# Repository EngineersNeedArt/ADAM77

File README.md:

# Adam77

A 40×24 ASCII serial terminal for early 8-bit computers such as the KIM-1. A USB keyboard plugs into the Teensy 4.1's USB host port. Text appears on a 320×240 ILI9341 TFT.

Adam77 follows [Adam74](https://github.com/EngineersNeedArt/Adam74). Adam74 took parallel ASCII in; Adam77 talks serial and adds a keyboard.

## Layout

| Path | What |
| --- | --- |
| `src/main.cpp` | Firmware |
| `lib/TextBuffer/` | Text grid class, from Adam74 |
| `lib/Fonts/` | Liberation Mono Bold, from Adam74 |
| `hardware/` | KiCad project (rough schematic; see below) |
| `platformio.ini` | Build configuration |

## Building

```bash
pio run              # build
pio run -t upload    # build and flash (Teensy Loader opens)
pio device monitor   # USB debug console
```

## Hardware (KiCad)

`hardware/ADAM77.kicad_pro` opens in KiCad 10. It's a rough first pass, generated rather than drawn by hand, so expect to tidy the layout.

- **The schematic** covers USB-C 5 V input (with CC pull-downs), the Teensy 4.1, the PAL-2 TTL header (74HC4050 on the PAL-2's output, polyfuse on its 5 V), the TFT header, the USB host jack and the LM386 audio section.
- **ERC:** no errors or warnings.
- **Through-hole parts** everywhere except the USB-C jack, whose six power-only pads are large enough to hand-solder. The level shifter is a **74HC4050** (DIP-16) instead of the 74LVC245, which isn't made in DIP. Powered at 3.3 V, its inputs accept 5 V and its outputs are 3.3 V. The polyfuse is the radial Bourns MF-RG1100.
- **The Teensy 4.1** symbol and footprint are in the project's own library (`ADAM77.kicad_sym`, `ADAM77.pretty`). The footprint covers the 48 outer pins only. The USB host pins come out on J4, a 5-pin header for a short cable from the Teensy, since their exact position on the Teensy isn't modeled.
- **To start the PCB:** open the PCB editor and choose Tools → Update PCB from Schematic (F8) to pull in all the footprints.
- **J2 (PAL-2):** 1 GND, 2 +5V, 3 `TTL (IN) KYBD`, 4 `TTL (OUT) PTR`. The PAL-2 has no standard cable, so make a 4-wire one to match.
- **J4 (USB host):** 5V, D−, D+, GND, GND, the same order as the Teensy 4.1's host pins.

## Loading files from the SD card

Put files on a microSD card (FAT16, FAT32 or exFAT), in folders if you like, and put it in the Teensy 4.1's own card socket. [sd/](sd/) has a ready-made set of KIM-1 paper tapes to copy onto a card. Cards can be swapped while Adam77 is on, as long as nothing is being sent.

1. At the KIM-1 monitor prompt, press **F2**. A list of the card's folders and files appears, folders first (in white, labeled FOLDER). The top line shows the folder you're in. Known types show their name without the extension, plus a type label. Files that are sent (TAPE, BASIC) are green; text files, which are only read, are dark green. The banners and the startup message are white. The selection bar is the selected entry's own color, inverted.
2. Choose one with the arrow keys (Page Up/Down and Home/End also work; holding an arrow repeats it), or type a letter or digit to jump to the next name starting with it. Then press **Enter**.
   - **Enter** (or Right arrow) on a folder opens it. **Esc**, Backspace or Left arrow goes back up a folder.
   - **Esc** in the top folder, or **F2** anywhere, goes back to the terminal. The next F2 opens the same folder again.
3. The file's extension decides what happens:

   | Extension | Type | What Enter does |
   | --- | --- | --- |
   | `.pap`, `.ptp` | TAPE | Sends it as a paper tape (MOS Technology format): types `L` first, putting the monitor in paper-tape load mode, then sends the tape with CR LF line ends. |
   | `.bas` | BASIC | Sends it as if typed, with CR line ends. |
   | `.txt` | TEXT | Shows it on the screen only; nothing goes to the KIM-1. |
   | anything else | | Sent as a paper tape if its first character is `;`, otherwise as if typed. |

4. Sending waits for the KIM-1's echo of each character before sending the next, so it runs as fast as the KIM-1 can take it. Press **Esc** to stop a send. A beep means it's finished.
5. A text file is word-wrapped to 40 columns. Scroll with the arrow keys, **Space** or Page Up/Down, and Home/End. **Esc** goes back to the file list; **F2** goes straight back to the terminal. Files over 64 KB are cut off.

A text file is a handy place for a program's instructions: put `slots.txt` (for example, "0200 G to start") next to `slots.pap`.

## Design notes

- **Serial:** Uses the Teensy's hardware UART (`Serial1`, pins 0/1) at 1200 baud 8N2. Nothing is bit-banged. The KIM-1 measures the baud rate from the first RUBOUT after reset, so any standard rate works.
- **Line interface (target: PAL-2):** The PAL-2 KIM-1 replica has a 5 V TTL serial port, the same kind its bundled USB-to-TTL adapter plugs into. Its idle line is high, as on a standard UART, so no inversion is needed. The Teensy 4.1's pins are **not 5 V tolerant**, so the PAL-2's TX line must be shifted down before it reaches Teensy RX1, for example by a 74HC4050 (DIP) or the 74LVC245 that Adam74 used. The Teensy's 3.3 V TX output is normally above a 5 V TTL input's 2.0 V high threshold, so that direction can connect directly. Adam77 takes the place of the PAL-2's USB-to-TTL adapter and uses the same four wires: TXD, RXD, 5 V and GND.
- **Power (decided):** Adam77 powers the PAL-2 through that 5 V wire, the same way the adapter does. One 5 V USB supply feeds Adam77's power jack and becomes the board's 5 V rail. That rail supplies:
  - the Teensy's VIN pin
  - the USB host port, for the keyboard
  - the PAL-2, through a resettable polyfuse

  Cut the VUSB–VIN trace on the Teensy so that a programming cable can't feed power back into the rail.

  **Measured:** the PAL-2's peak draw was 476 mA, including its USB-to-TTL adapter. That was measured while it loaded a paper tape over serial and ran a game with LED animation.

  | Load | Typical | Worst case |
  | --- | --- | --- |
  | PAL-2 | 480 mA | 480 mA |
  | Teensy 4.1 (600 MHz) | 100 mA | 120 mA |
  | ILI9341 TFT and backlight | 80 mA | 100 mA |
  | USB keyboard | 20–100 mA | 500 mA (USB limit; backlit keyboards) |
  | **Total** | **~0.75 A** | **~1.2 A** |

  - **Supply:** use a USB-C 5 V supply rated at least 2 A; 3 A is preferred. The board's USB-C jack needs 5.1 kΩ pull-downs on CC1 and CC2, or USB-C chargers won't turn on their 5 V output.
  - **PAL-2 fuse:** a polyfuse that holds 1.1 A and trips at 2.2 A, such as the Bourns MF-RG1100 (radial, through-hole) or MF-MSMF110 (1812 surface mount). The 476 mA peak is under half the hold rating. Its resistance drops only about 0.07 V at that current. A 0.75 A part would also work, but drops about twice as much voltage.
  - **Keyboard port:** the Teensy 4.1's USB host header has its own current-limit switch, powered from VIN, so the PCB only needs a USB-A jack wired to the header.
- **PAL-1:** Not the same interface. The PAL-1 adds a small discrete-transistor stage after the KIM-1 current loop to produce RS-232 levels on a DB-9 wired as DCE (data communications equipment). Supporting it would need an RS-232 transceiver such as the MAX3232 as an option.
- **Board (decided): Teensy 4.1.** It has the same 600 MHz chip as the 4.0. We chose it for two things: the USB host header, which has current limiting built in, and the microSD socket, which could hold paper-tape files for Adam77 to send to the PAL-2 with echo pacing.
- **Scrolling:** The ILI9341 scrolls in hardware only along its native 320-pixel axis, which is horizontal in landscape mode. That's why Adam74 couldn't scroll vertically. A RAM framebuffer with DMA updates (`ILI9341_t3n`) is the likely fix: 150 KB fits easily in the Teensy 4.1's RAM.

## Future ideas

None of these are decided yet.

- **Audio in: LM386 mixer and speaker.** A PAL-2 port pin and the Teensy's bell pin share one speaker and one volume pot. Then programs such as MUSICBOX from *The First Book of KIM* play without another board. The LM386 is an 8-pin audio amplifier that runs from 5 V and drives an 8 Ω speaker at about ½ W; a plain op-amp can't drive a speaker directly.

  ```
  Teensy pin 19 ──1 µF──47 kΩ──┐
                               ├──── pot top (10 kΩ log)
  PAL-2 port pin ─1 µF──47 kΩ──┘     pot wiper ──→ LM386 IN+ (pin 3)
                                     pot bottom ──→ GND
                                                   LM386 IN− (pin 2) → GND

  LM386 OUT (pin 5) ──220 µF (+ toward LM386)──→ speaker (8 Ω) ──→ GND
                    └─10 Ω──0.05 µF──→ GND       (keeps it from oscillating)
  LM386 pin 6 → 5 V, with 100 µF + 0.1 µF to GND close to the chip
  LM386 pin 7 → 10 µF to GND                     (cuts supply noise)
  LM386 pin 4 → GND
  ```

  - The 1 µF capacitors block DC, so it doesn't matter whether a pin idles high or low.
  - The 47 kΩ resistors mix the two sources, keep their outputs from fighting, and cut the full-volume square waves down for the LM386's gain of 20. Increase them if it's too loud at the bottom of the pot.
  - The PAL-2's 5 V signal meets only resistors and capacitors, never a Teensy pin. Its ground comes through the TTL cable.
  - The speaker replaces the piezo. Pin 19 and the firmware stay the same.
  - If digital noise from the shared 5 V rail comes through as a buzz, filter the LM386's supply: 10 Ω in series and another 100 µF to GND.
- **DB-9 RS-232 port.** A MAX3232 transceiver and a DB-9 wired as DTE, like a PC's serial port, so a straight cable reaches DCE machines such as the PAL-1. Keep the TTL header for the PAL-2: the TTL header on `Serial1`, the DB-9 on `Serial2`, and a setting picks the active one.
- **Settings screen.** Instead of DIP switches: a key such as F1 opens a settings screen, with the choices saved in the Teensy's EEPROM. Settings: baud rate, data bits / parity / stop bits, which port, local echo, adding LF after CR, upper-case only, text color. Holding a key at power-up restores the defaults. Fuller support for other machines would eventually need a subset of cursor-control codes, such as VT52 or ADM-3A.
- **More from the SD card.** The basic loader works (see "Loading files from the SD card"). Still to do: folders, Intel HEX converted to MOS paper-tape format as it's sent, and capturing a tape the PAL-2 punches with `Q` into a new file.

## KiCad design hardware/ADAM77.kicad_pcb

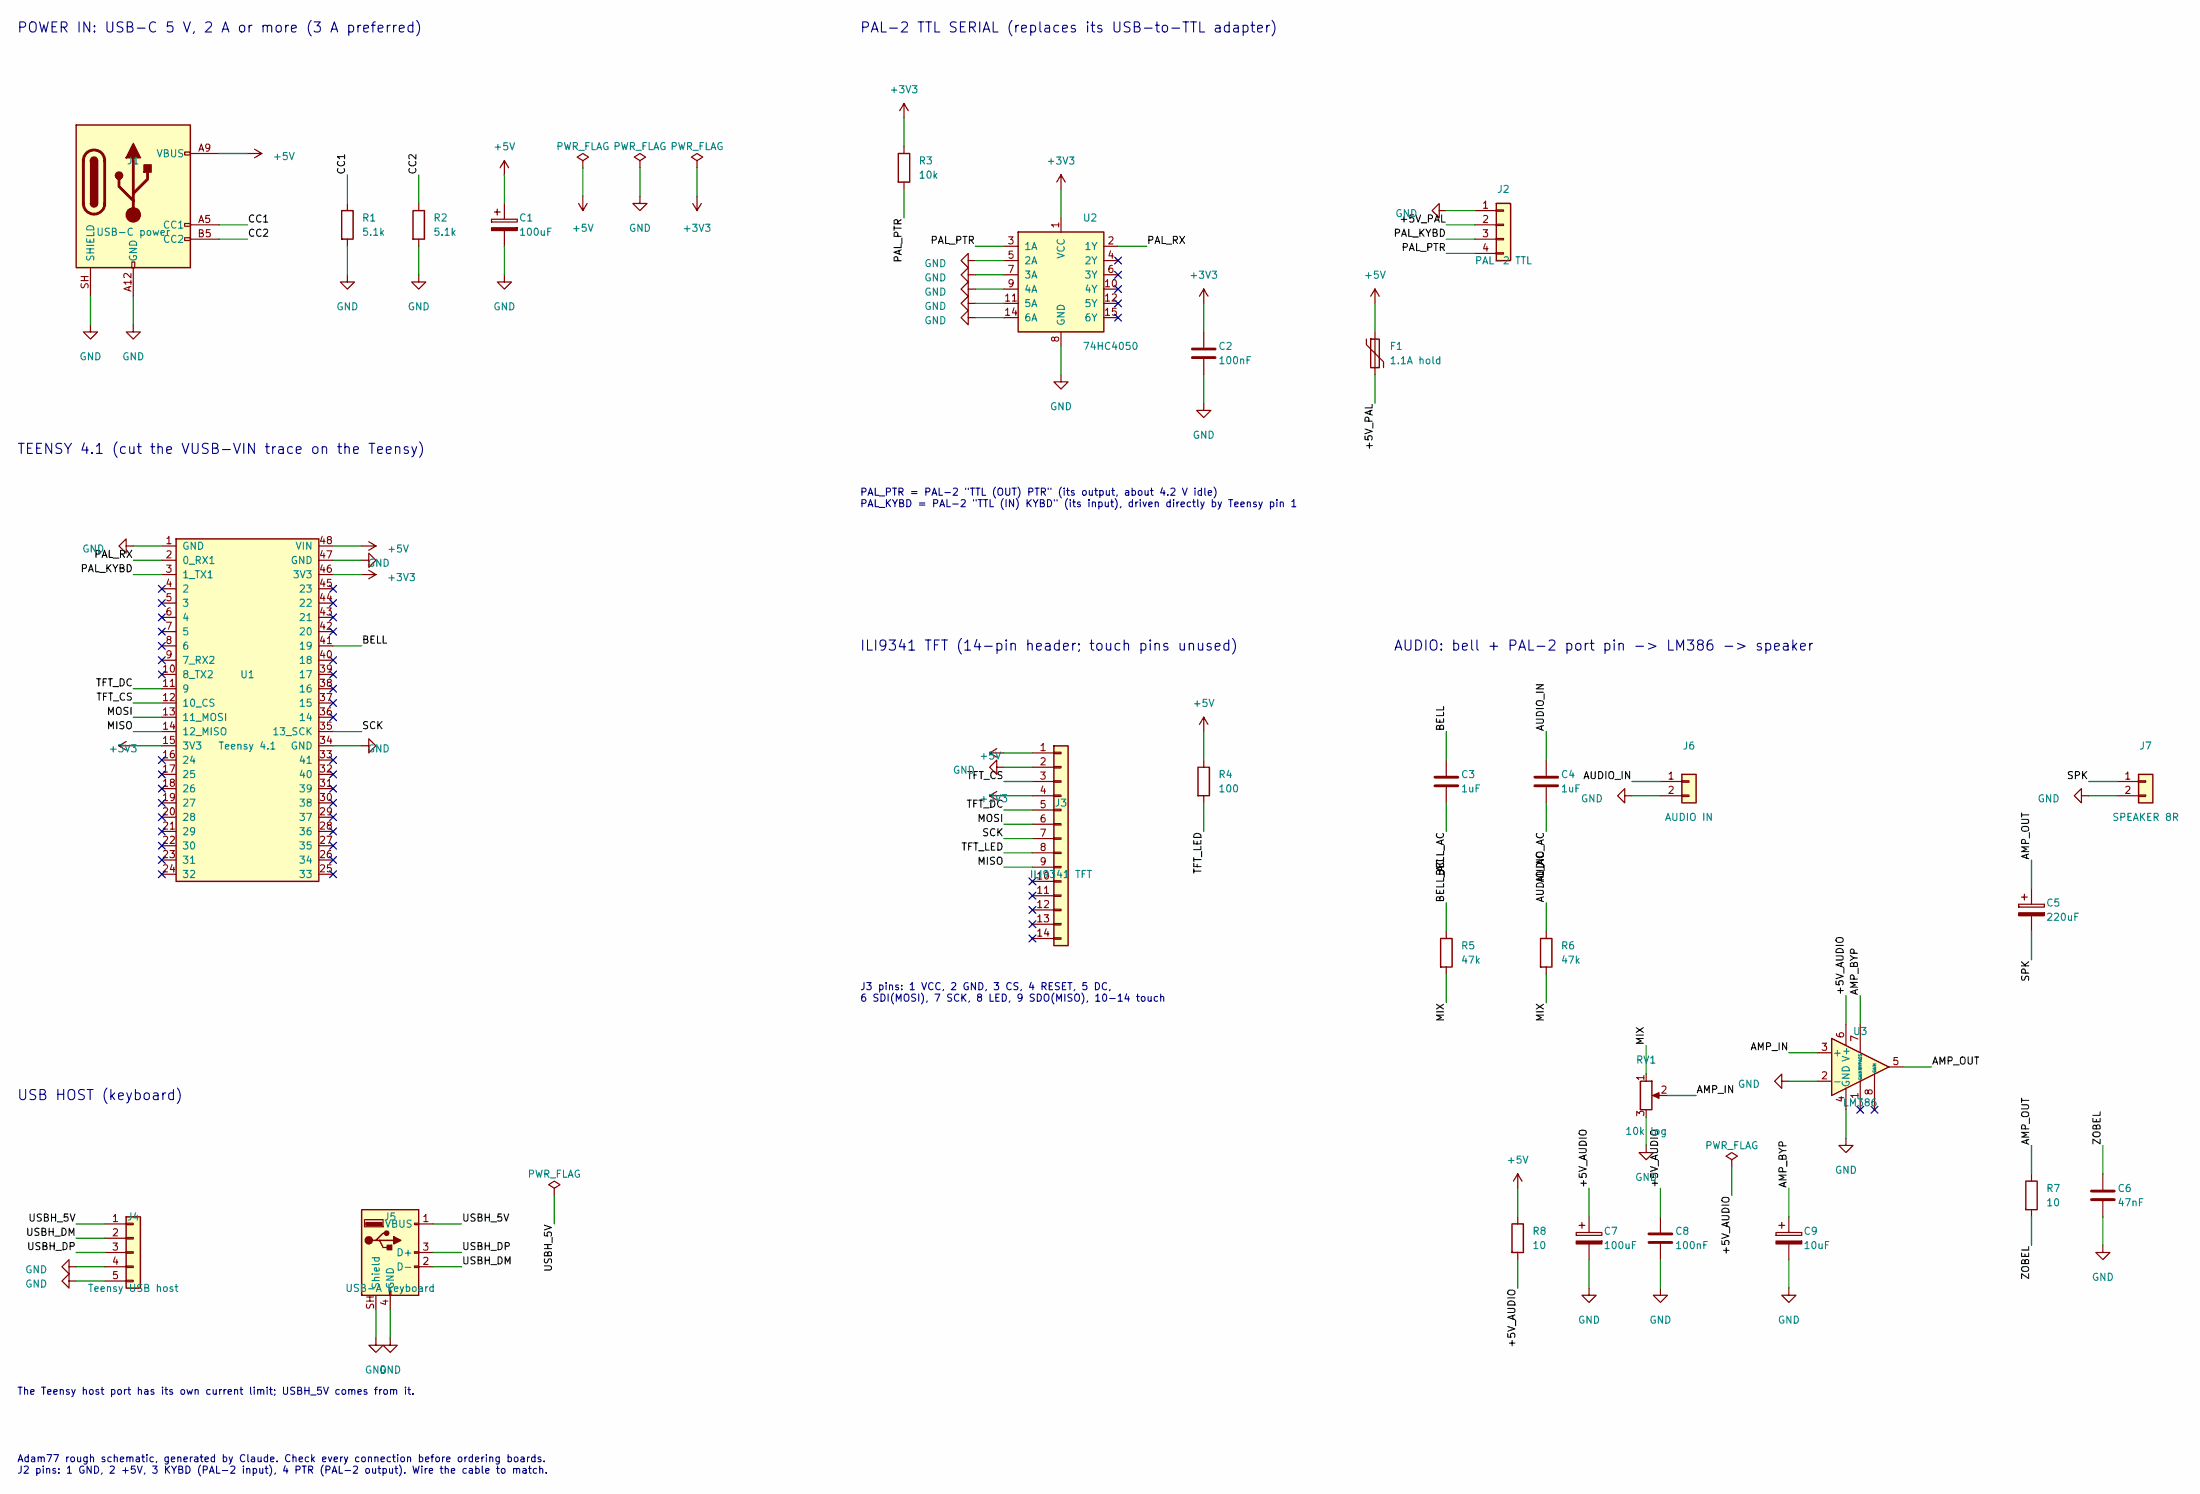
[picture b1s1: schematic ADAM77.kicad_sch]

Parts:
C1, C7: 100uF; CP_Radial_D6.3mm_P2.50mm
C2, C8: 100nF; C_Disc_D5.0mm_W2.5mm_P5.00mm
C3, C4: 1uF; C_Disc_D5.0mm_W2.5mm_P5.00mm
C5: 220uF; CP_Radial_D8.0mm_P3.50mm
C6: 47nF; C_Disc_D5.0mm_W2.5mm_P5.00mm
C9: 10uF; CP_Radial_D5.0mm_P2.00mm
F1: 1.1A hold; Fuse_Bourns_MF-RG1100
J1: USB-C power; USB_C_Receptacle_GCT_USB4125-xx-x_6P_TopMnt_Horizontal
J2: PAL-2 TTL; PinHeader_1x04_P2.54mm_Vertical
J3: ILI9341 TFT; PinSocket_1x14_P2.54mm_Vertical
J4: Teensy USB host; PinHeader_1x05_P2.54mm_Vertical
J5: USB-A keyboard; USB_A_Molex_67643_Horizontal
J6: AUDIO IN; PinHeader_1x02_P2.54mm_Vertical
J7: SPEAKER 8R; PinHeader_1x02_P2.54mm_Vertical
R1, R2: 5.1k; R_Axial_DIN0207_L6.3mm_D2.5mm_P10.16mm_Horizontal
R3: 10k; R_Axial_DIN0207_L6.3mm_D2.5mm_P10.16mm_Horizontal
R4: 100; R_Axial_DIN0207_L6.3mm_D2.5mm_P10.16mm_Horizontal
R5, R6: 47k; R_Axial_DIN0207_L6.3mm_D2.5mm_P10.16mm_Horizontal
R7, R8: 10; R_Axial_DIN0207_L6.3mm_D2.5mm_P10.16mm_Horizontal
RV1: 10k log; Potentiometer_Alps_RK09K_Single_Vertical
U1: Teensy 4.1; Teensy_4.1
U2: 74HC4050; DIP-16_W7.62mm_Socket
U3: LM386; DIP-8_W7.62mm_Socket

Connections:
+3V3: C2.1, J3.4, R3.1, U1.15 (3V3), U1.46 (3V3), U2.1 (VCC)
+5V: C1.1, F1.1, J1.A9 (VBUS), J1.B9 (VBUS), J3.1, R4.1, R8.1, U1.48 (VIN)
/+5V_AUDIO: C7.1, C8.1, R8.2, U3.6 (V+)
/+5V_PAL: F1.2, J2.2
/AMP_BYP: C9.1, U3.7 (BYPASS)
/AMP_IN: RV1.2, U3.3 (+)
/AMP_OUT: C5.1, R7.1, U3.5
/AUDIO_AC: C4.2, R6.1
/AUDIO_IN: C4.1, J6.1
/BELL: C3.1, U1.41 (19)
/BELL_AC: C3.2, R5.1
/CC1: J1.A5 (CC1), R1.1
/CC2: J1.B5 (CC2), R2.1
/MISO: J3.9, U1.14 (12_MISO)
/MIX: R5.2, R6.2, RV1.1
/MOSI: J3.6, U1.13 (11_MOSI)
/PAL_KYBD: J2.3, U1.3 (1_TX1)
/PAL_PTR: J2.4, R3.2, U2.3 (1A)
/PAL_RX: U1.2 (0_RX1), U2.2 (1Y)
/SCK: J3.7, U1.35 (13_SCK)
/SPK: C5.2, J7.1
/TFT_CS: J3.3, U1.12 (10_CS)
/TFT_DC: J3.5, U1.11 (9)
/TFT_LED: J3.8, R4.2
/USBH_5V: J4.1, J5.1 (VBUS)
/USBH_DM: J4.2, J5.2 (D-)
/USBH_DP: J4.3, J5.3 (D+)
/ZOBEL: C6.1, R7.2
GND: C1.2, C2.2, C6.2, C7.2, C8.2, C9.2, J1.A12 (GND), J1.B12 (GND), J1.SH (SHIELD), J2.1, J3.2, J4.4, J4.5, J5.4 (GND), J5.SH (Shield), J6.2, J7.2, R1.2, R2.2, RV1.3, U1.1 (GND), U1.34 (GND), U1.47 (GND), U2.5 (2A), U2.7 (3A), U2.8 (GND), U2.9 (4A), U2.11 (5A), U2.14 (6A), U3.2 (-), U3.4 (GND)

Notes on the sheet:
POWER IN: USB-C 5 V, 2 A or more (3 A preferred)
TEENSY 4.1 (cut the VUSB-VIN trace on the Teensy)
PAL-2 TTL SERIAL (replaces its USB-to-TTL adapter)
PAL_PTR = PAL-2 "TTL (OUT) PTR" (its output, about 4.2 V idle) PAL_KYBD = PAL-2 "TTL (IN) KYBD" (its input), driven directly by Teensy pin 1
ILI9341 TFT (14-pin header; touch pins unused)
J3 pins: 1 VCC, 2 GND, 3 CS, 4 RESET, 5 DC, 6 SDI(MOSI), 7 SCK, 8 LED, 9 SDO(MISO), 10-14 touch
USB HOST (keyboard)
The Teensy host port has its own current limit; USBH_5V comes from it.
AUDIO: bell + PAL-2 port pin -> LM386 -> speaker
Adam77 rough schematic, generated by Claude. Check every connection before ordering boards. J2 pins: 1 GND, 2 +5V, 3 KYBD (PAL-2 input), 4 PTR (PAL-2 output). Wire the cable to match.

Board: 2 copper layers, 29 parts (0 on the bottom side), 29 nets, no tracks yet.
